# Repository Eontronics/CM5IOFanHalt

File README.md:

# CM5 IO Board Fan Halt
A small, low cost add-on module for the Raspberry Pi Compute Module 5 IO Board to halt the fan from spinning after shutting the Pi down!
Development logs of the hardware can be found on the [Hackaday.io project page](https://hackaday.io/project/202403-cm5-io-board-fan-halt).

## What is it for?
After shutting down the Raspberry Pi Compute module 5, the fan control PWM signal is allowed to float high. 
As a result, the fan ramps up to full speed after turning everything else off, and the only way to stop it is to unplug the power.
Annoying!

This module can be attached directly to the Compute Module 5 IO board, and electrically sits betwween the fan header and the fan.
When it detects the Pi has been shutdown, it also automatically cuts power to the fan to keep it from spinning up and making noise.

## How does it work?
The module monitors the voltage on he 'CM5_3.3V' rail of the Compute Module 5 to determine whether it is an active or shutdown state.
Conveniently, this rail drives the pullup resistor on the 'Fan_Tacho' pin, so it is possible to monitor it through the fan header.

By monitoring how long it has been since this pin was pulled high, it can detect whether 'CM5_3.3V' is powered, while ignoring brief
'low' pulses that occur when the signal is pulled down through the fan tachometer. This then drives a high side transistor to either
provide or cut power to the fan.

## Show me that it works!
Don't just take my word for it, I've linked a short video [here](https://www.youtube.com/watch?v=HvpnCyq3iTY) to demonstrate that the module does what it's supposed to do!

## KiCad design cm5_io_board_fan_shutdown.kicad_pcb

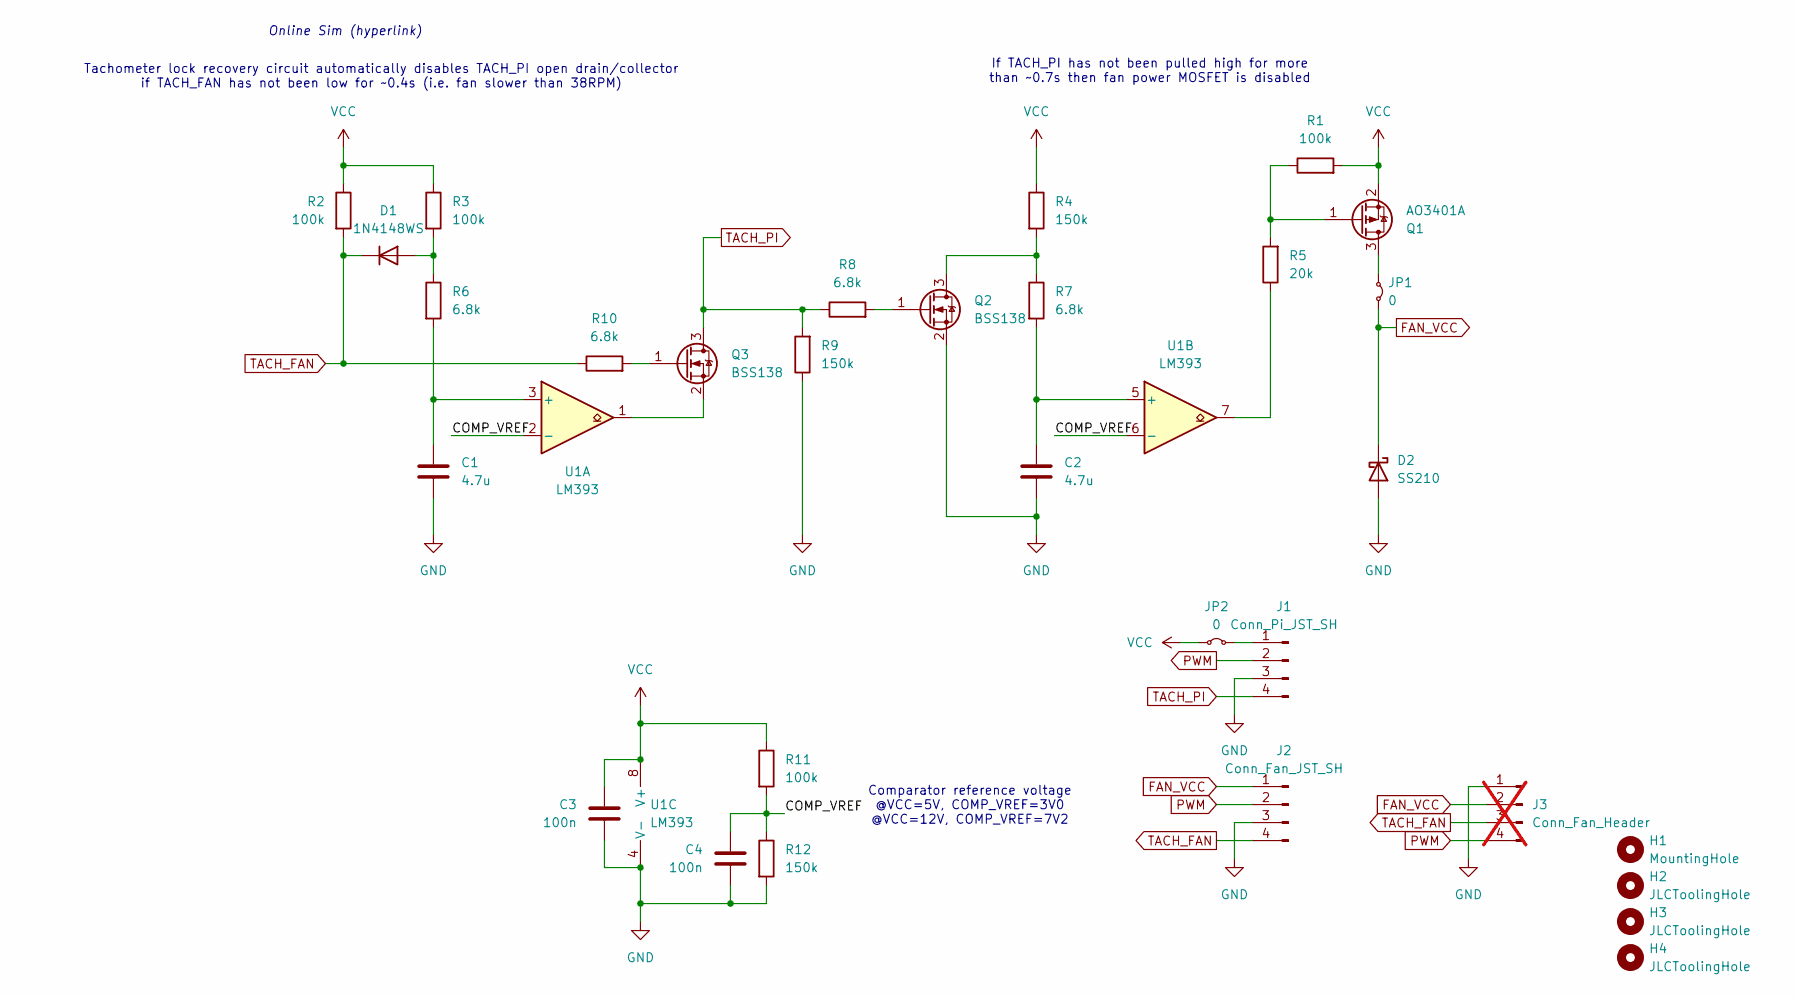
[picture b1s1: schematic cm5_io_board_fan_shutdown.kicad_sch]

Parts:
C1, C2: 4.7u; C_0603_1608Metric
C3, C4: 100n; C_0603_1608Metric
D1: 1N4148WS; D_SOD-323
D2: SS210; D_SMA
H1: MountingHole; MountingHole_2.7mm_M2.5_DIN965
H2, H3, H4: JLCToolingHole; JLC_Tooling_Hole
J1: Conn_Pi_JST_SH; JST_SH_BM04B-SRSS-TB_1x04-1MP_P1.00mm_Vertical
J2: Conn_Fan_JST_SH; JST_SH_BM04B-SRSS-TB_1x04-1MP_P1.00mm_Vertical
J3: Conn_Fan_Header; PinHeader_1x04_P2.54mm_Vertical_SMD_Pin1Left; not fitted
JP1, JP2: 0; R_1206_3216Metric
Q1: AO3401A; SOT-23
Q2, Q3: BSS138; SOT-23
R1, R2, R3, R11: 100k; R_0603_1608Metric
R4, R9, R12: 150k; R_0603_1608Metric
R5: 20k; R_0603_1608Metric
R6, R7, R8, R10: 6.8k; R_0603_1608Metric
U1: LM393; SOIC-8_3.9x4.9mm_P1.27mm

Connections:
/COMP_VREF: C4.1, R11.2, R12.1, U1.2 (-), U1.6 (-)
FAN_VCC: D2.1 (K), J2.1, J3.2, JP1.2 (B)
GND: C1.2, C2.2, C3.2, C4.2, D2.2 (A), J1.3, J2.3, J3.1, Q2.2 (S), R9.1, R12.2, U1.4 (V-)
unnamed: D1.2 (A), R3.2, R6.1
unnamed: J1.1, JP2.2 (B)
unnamed: JP1.1 (A), Q1.3 (D)
unnamed: Q1.1 (G), R1.1, R5.2
unnamed: Q2.3 (D), R4.2, R7.1
unnamed: Q2.1 (G), R8.2
unnamed: Q3.1 (G), R10.2
unnamed: Q3.2 (S), U1.1
unnamed: R5.1, U1.7
unnamed: C1.1, R6.2, U1.3 (+)
unnamed: C2.1, R7.2, U1.5 (+)
PWM: J1.2, J2.2, J3.4
TACH_FAN: D1.1 (K), J2.4, J3.3, R2.2, R10.1
TACH_PI: J1.4, Q3.3 (D), R8.1, R9.2
VCC: C3.1, JP2.1 (A), Q1.2 (S), R1.2, R2.1, R3.1, R4.1, R11.1, U1.8 (V+)

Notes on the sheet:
Comparator reference voltage @VCC=5V, COMP_VREF=3V0 @VCC=12V, COMP_VREF=7V2
Online Sim (hyperlink)
Tachometer lock recovery circuit automatically disables TACH_PI open drain/collector if TACH_FAN has not been low for ~0.4s (i.e. fan slower than 38RPM)
If TACH_PI has not been pulled high for more than ~0.7s then fan power MOSFET is disabled

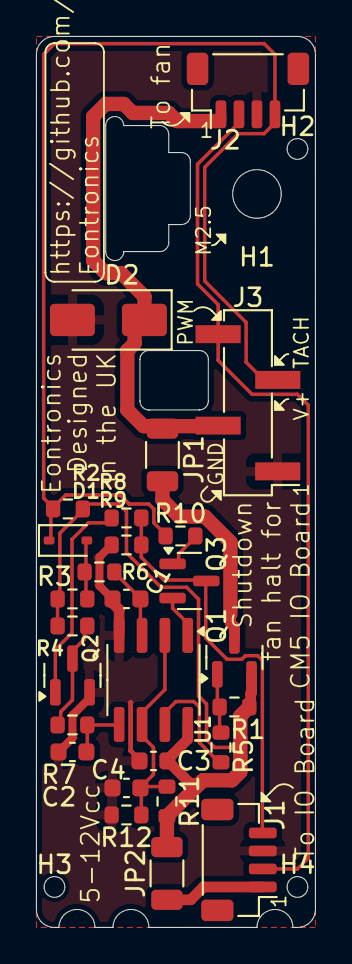
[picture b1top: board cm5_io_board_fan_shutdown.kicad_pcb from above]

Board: 2 copper layers, 15.5 x 49.5 mm, 32 parts (1 on the bottom side), 18 nets.

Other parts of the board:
QR*****: GithubQR

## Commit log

2025-02-02 added kicad .lck files to gitignore
2025-02-02 [fix_output_drive] flipped output FET, added voltage divider in output driver schematic
    Output P-FET has been flipped so it should no longer conduct through body diode when off, gate resistor has been changed to form voltage divider with pullup to limit VGS to ~10V when operating from 1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
2025-02-02 [fix_output_drive] Updated PCB layout to reflect output FET flip in schematic and resistor divider on gate
2025-02-02 [fix_output_drive] Updated silkscreen references to reduce overlapping, adjusted position of text slightly
2025-02-04 [update_to_v0.2] set grid origin point to bottom left corner of PCB
2025-02-04 [update_to_v0.2] updated SOT-23 footprints to match KiCAD library versions
    DRC highlighed SOT-23 footprints did not match version in library, these have been updated to clear DRC error despite appearing visually the same
2025-02-04 [update_to_v0.2] Updated version number in silkscreen to revision 0.2, changed QR code to point to project repo
2025-02-05 Removed .kicad_prl file and added to .gitignore
2025-02-09 Added renders and PDFs of schematic/PCB for viewing without KiCAD
2025-02-09 Added header image to README.md
2025-04-02 Added front photo of assembled v0.2 board
2025-04-02 Replaced header image in README.md with PCB photo + links to Hackaday project & demo video
2025-04-02 Fix typos in README.md
